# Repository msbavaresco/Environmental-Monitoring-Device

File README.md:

# Environmental Monitoring Device
This project is a device that measures CO2 concentration, temperature and relative humididty using Sensirion's SCD4x sensor and a Raspberry Pi Zero W. The data is then stored internally and, optionally, transmitted via MQTT.

## Hardware Requirements
- Raspberry Pi Zero W
- Sensirion SCD41 or SCD40 sensor

## Wiring
| SCD4x Pin | Raspberry Pi Pin |
|-----------|------------------|
| VCC       | 3.3V             |
| GND       | GND              |
| SDA       | GPIO2 (Pin 3)    |
| SCL       | GPIO3 (Pin 5)    |

## Installation

### 1. Clone the repository

```bash
git clone https://github.com/msbavaresco/Environmental-Monitoring-Device.git
cd Environmental-Monitoring-Device
```

### 2. Install required packages

```bash
sudo apt update
sudo apt install -y \
    build-essential \
    gcc \
    g++ \
    make \
    libpaho-mqttpp3-dev \
    nlohmann-json3-dev
```

### 3. Enable I2C on the Raspberry Pi

Run:

```bash
sudo raspi-config
```

Then go to:

```text
Interface Options -> I2C -> Enable
```

Reboot:

```bash
sudo reboot
```

After reboot, return to the project folder:

```bash
cd Environmental-Monitoring-Device
```

### 4. Create the configuration directory

```bash
sudo mkdir -p /var/lib/ThisDevice
```

### 5. Copy the example configuration file

```bash
sudo cp Source/config/config.example.json /var/lib/ThisDevice/config.json
```

### 6. Edit the configuration file

```bash
sudo nano /var/lib/ThisDevice/config.json
```

Example:

```json
{
  "wifi": {
    "configured": true,
    "ssid": "MyWifi"
  },
  "mqtt": {
    "host": "192.168.1.50",
    "port": 1883,
    "username": "",
    "password": "",
    "base_topic": "env"
  },
  "device": {
    "location": "office"
  }
}
```

### 7. Build the project

```bash
cd Source
make
```

### 8. Run the program

```bash
./bin/project
```

## Notes

- The configuration file must exist at `/var/lib/ThisDevice/config.json`
- I²C must be enabled or the sensor will not work
- Update the MQTT settings and device location before running

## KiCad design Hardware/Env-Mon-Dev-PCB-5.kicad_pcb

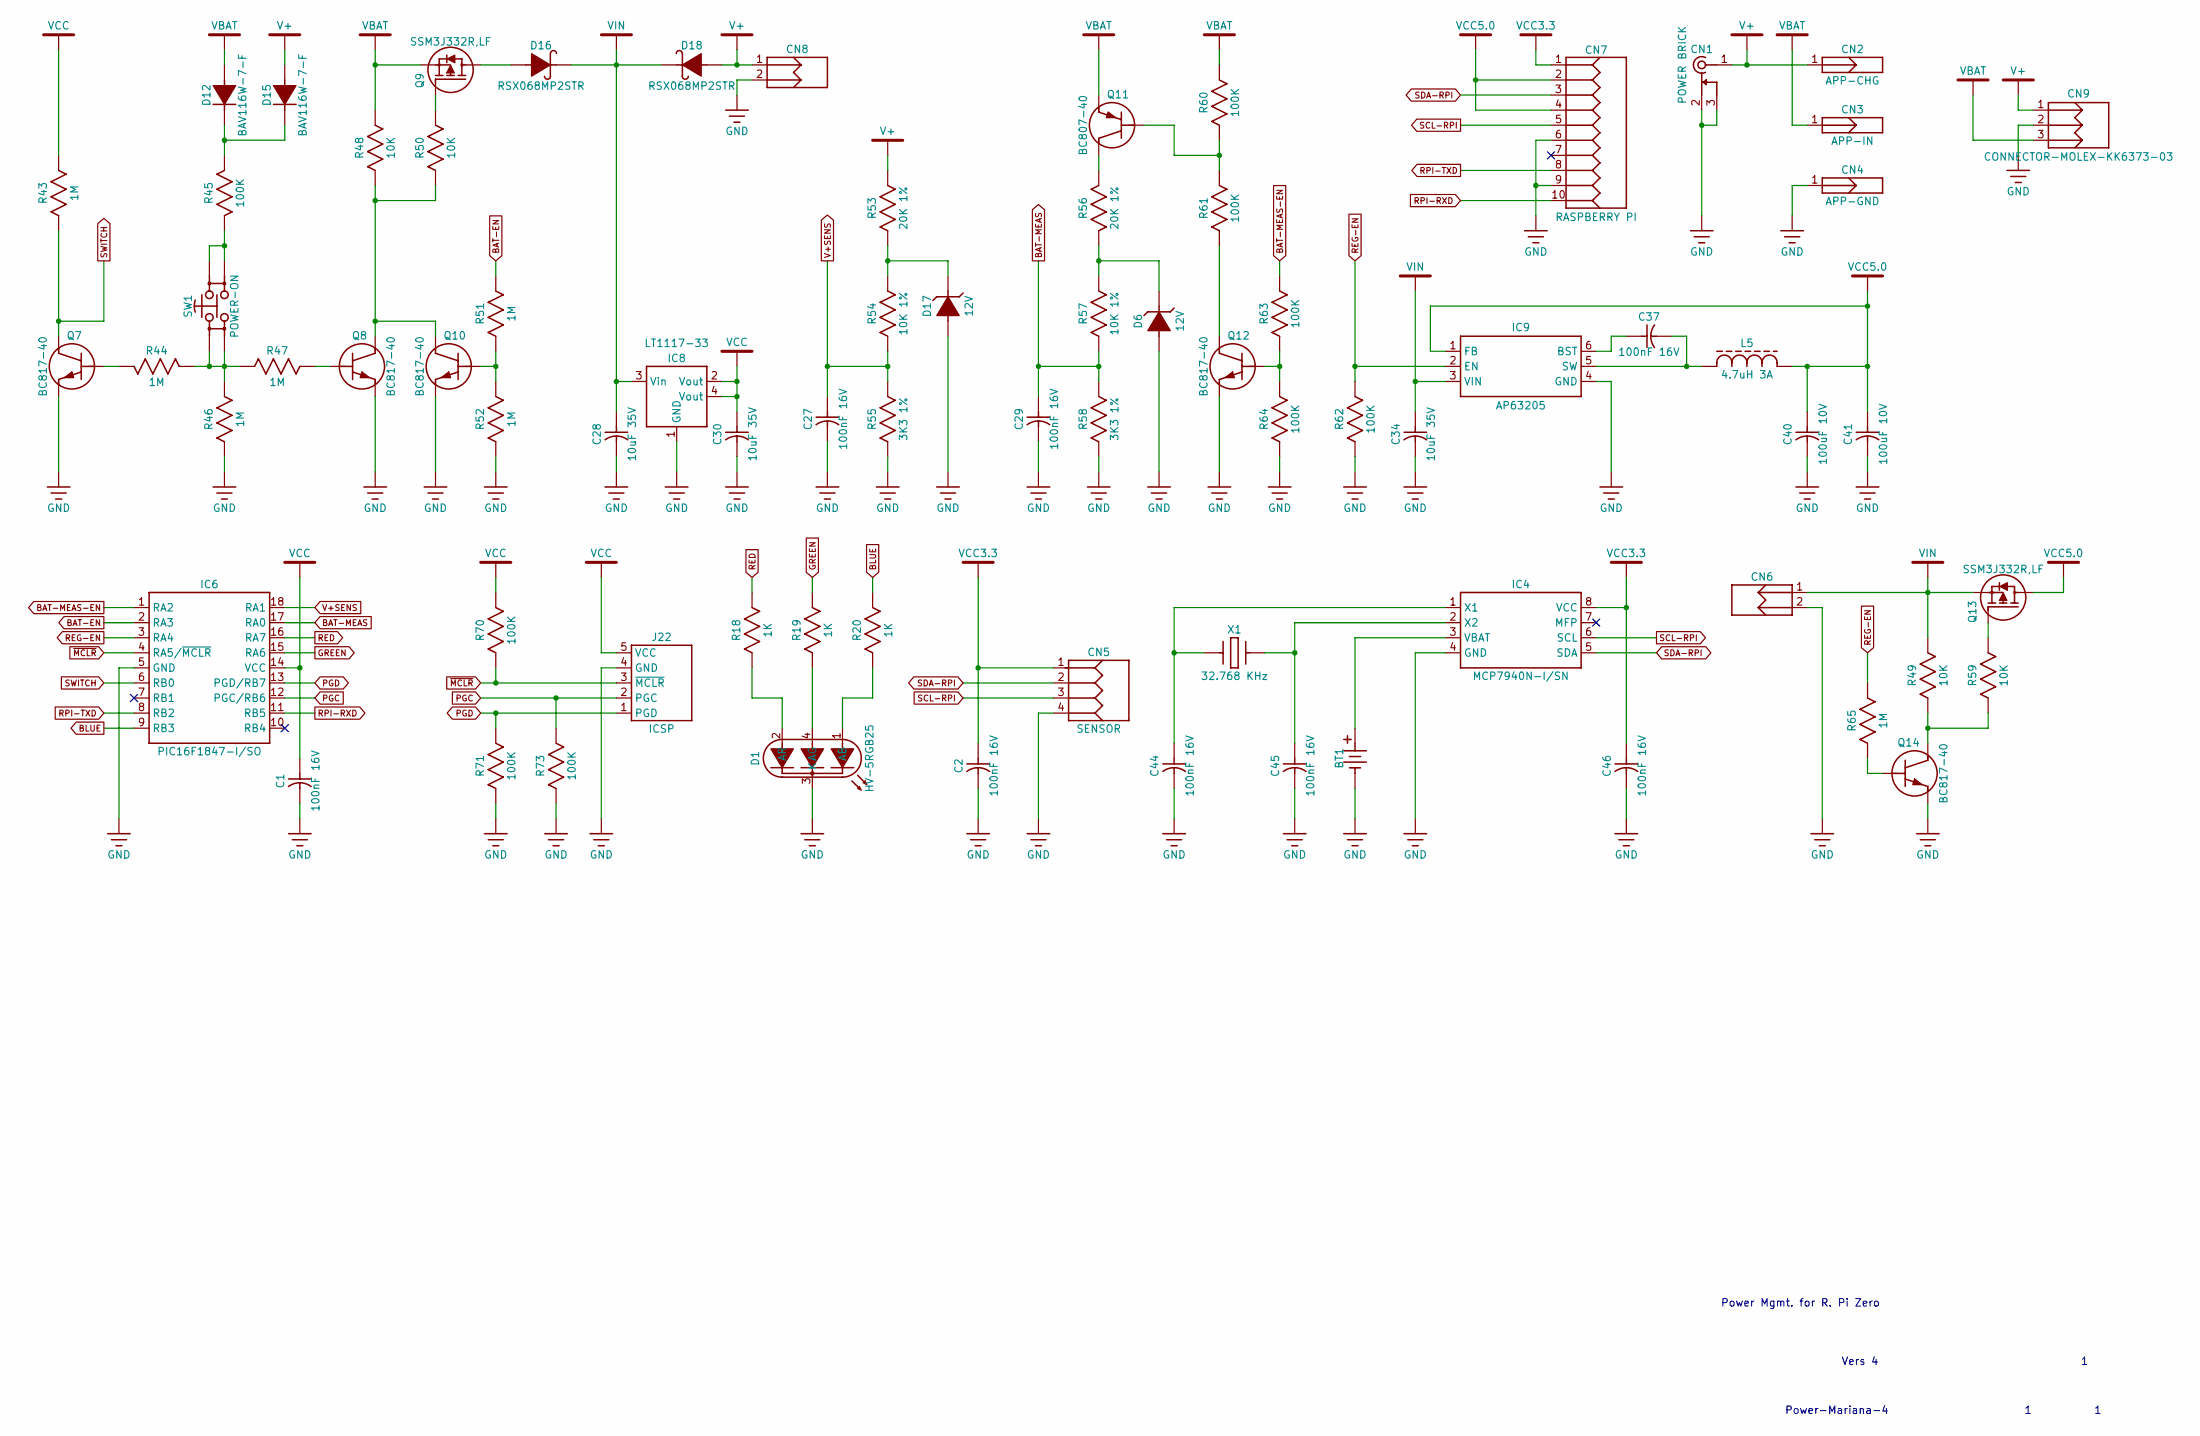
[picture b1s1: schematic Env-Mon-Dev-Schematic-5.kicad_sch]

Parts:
BT1: SOCKET-BATTERY-CR2032
C1, C2, C27, C29, C37, C44, C45, C46: 100nF 16V; CAPACITOR-CC0603R
C28, C30, C34: 10uF 35V; CAPACITOR-CC0805R
C40, C41: 100uF 10V; CAPACITOR-CC1210R
CN1: POWER BRICK; CONNECTOR-JACK-J4-HORIZ
CN2: APP-CHG; CONNECTOR-POGO-01-D3.0H1.0
CN3: APP-IN; CONNECTOR-POGO-01-D3.0H1.0
CN4: APP-GND; CONNECTOR-POGO-01-D3.0H1.0
CN5: SENSOR; CONNECTOR-RECEPTACLE-1X4-P2.54
CN6, CN8: CONNECTOR-MOLEX-KK6373-02
CN7: RASPBERRY PI; CONNECTOR-RECEPTACLE-2X5-P2.54
CN9: CONNECTOR-MOLEX-KK6373-03
D1: HV-5RGB25; LED-RGB-D5.00-P1.588-4P
D6, D17: 12V; SOD-123
D12, D15: BAV116W-7-F; SOD-123
D16, D18: RSX068MP2STR; SOD-123
IC4: MCP7940N-I/SN; SOIC-08-150
IC6: PIC16F1847-I/SO; SOIC-18-300
IC8: LT1117-33; SOT-223
IC9: AP63205; SOT-23-6
J22: ICSP; CONNECTOR-HEADER-1X5-P2.54
L5: 4.7uH 3A; INDUCTOR-FERRITE-NRS6045T
Q7, Q8, Q10, Q12, Q14: BC817-40; SOT-23
Q9, Q13: SSM3J332R,LF; SOT-23
Q11: BC807-40; SOT-23
R18, R19, R20: 1K; RESISTOR-RC0603R
R43, R44, R46, R47, R51, R52, R65: 1M; RESISTOR-RC0603R
R45, R60, R61, R62, R63, R64, R70, R71, R73: 100K; RESISTOR-RC0603R
R48, R49, R50, R59: 10K; RESISTOR-RC0603R
R53, R56: 20K 1%; RESISTOR-RC0805R
R54, R57: 10K 1%; RESISTOR-RC0603R
R55, R58: 3K3 1%; RESISTOR-RC0603R
SW1: POWER-ON; SWITCH-TACTILE-MINI-VERTICAL
X1: 32.768 KHz; CRYSTAL-3.20X1.50-2P

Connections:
BAT-EN: IC6.2 (RA3), R51.2
BAT-MEAS: C29.1, IC6.17 (RA0), R57.1, R58.2
BAT-MEAS-EN: IC6.1 (RA2), R63.2
BLUE: IC6.9 (RB3), R20.2
GND: BT1.2 (-), C1.2, C2.2, C27.2, C28.2, C29.2, C30.2, C34.2, C40.2, C41.2, C44.2, C45.2, C46.2, CN1.2, CN1.3, CN4.1, CN5.4, CN6.2, CN7.6, CN7.9, CN8.2, CN9.2, D1.3 (K), D6.A, D17.A, IC4.4 (GND), IC6.5 (GND), IC8.1 (GND), IC9.4 (GND), J22.4 (GND), Q7.2 (E), Q8.2 (E), Q10.2 (E), Q12.2 (E), Q14.2 (E), R46.1, R52.1, R55.1, R58.1, R62.1, R64.1, R71.1, R73.1
GREEN: IC6.15 (RA6), R19.2
unnamed: BT1.1 (+), IC4.3 (VBAT)
unnamed: D1.1 (AB), R20.1
unnamed: D1.4 (AG), R19.1
unnamed: D1.2 (AR), R18.1
unnamed: D6.K, R56.2, R57.2
unnamed: D12.K, D15.K, R45.1
unnamed: D17.K, R53.1, R54.2
unnamed: C44.1, IC4.1 (X1), X1.1
unnamed: C45.1, IC4.2 (X2), X1.2
unnamed: C37.1, IC9.6 (BST)
unnamed: C37.2, IC9.5 (SW), L5.1
unnamed: Q7.1 (B), R44.2
unnamed: Q8.1 (B), R47.2
unnamed: D16.A, Q9.3 (D)
unnamed: Q9.1 (G), R50.2
unnamed: Q10.1 (B), R51.1, R52.2
unnamed: Q8.3 (C), Q10.3 (C), R48.1, R50.1
unnamed: Q11.1 (B), R60.1, R61.2
unnamed: Q11.3 (C), R56.1
unnamed: Q12.1 (B), R63.1, R64.2
unnamed: Q12.3 (C), R61.1
unnamed: Q13.1 (G), R59.2
unnamed: Q14.1 (B), R65.1
unnamed: Q14.3 (C), R49.1, R59.1
unnamed: R44.1, R46.2, R47.1, SW1.3, SW1.4
unnamed: R45.2, SW1.1, SW1.2
PGC: IC6.12 (PGC/RB6), J22.2 (PGC), R73.2
PGD: IC6.13 (PGD/RB7), J22.1 (PGD), R71.2
RED: IC6.16 (RA7), R18.2
REG-EN: IC6.3 (RA4), IC9.2 (EN), R62.2, R65.2
RPI-RXD: CN7.10, IC6.11 (RB5)
RPI-TXD: CN7.8, IC6.8 (RB2)
SCL-RPI: CN5.3, CN7.5, IC4.6 (SCL)
SDA-RPI: CN5.2, CN7.3, IC4.5 (SDA)
SWITCH: IC6.6 (RB0), Q7.3 (C), R43.1
V+: CN1.1, CN2.1, CN8.1, CN9.1, D15.A, D18.A, R53.2
V+SENS: C27.1, IC6.18 (RA1), R54.1, R55.2
VBAT: CN3.1, CN9.3, D12.A, Q9.2 (S), Q11.2 (E), R48.2, R60.2
VCC: C1.1, C30.1, IC6.14 (VCC), IC8.2 (Vout), IC8.4 (Vout), J22.5 (VCC), R43.2, R70.2
VCC3.3: C2.1, C46.1, CN5.1, CN7.1, IC4.8 (VCC)
VCC5.0: C40.1, C41.1, CN7.2, CN7.4, IC9.1 (FB), L5.2, Q13.3 (D)
VIN: C28.1, C34.1, CN6.1, D16.K, D18.K, IC8.3 (Vin), IC9.3 (VIN), Q13.2 (S), R49.2
~MCLR: IC6.4 (RA5/~MCLR), J22.3 (~MCLR), R70.1

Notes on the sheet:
Power Mgmt. for R. Pi Zero
Vers 4
Power-Mariana-4

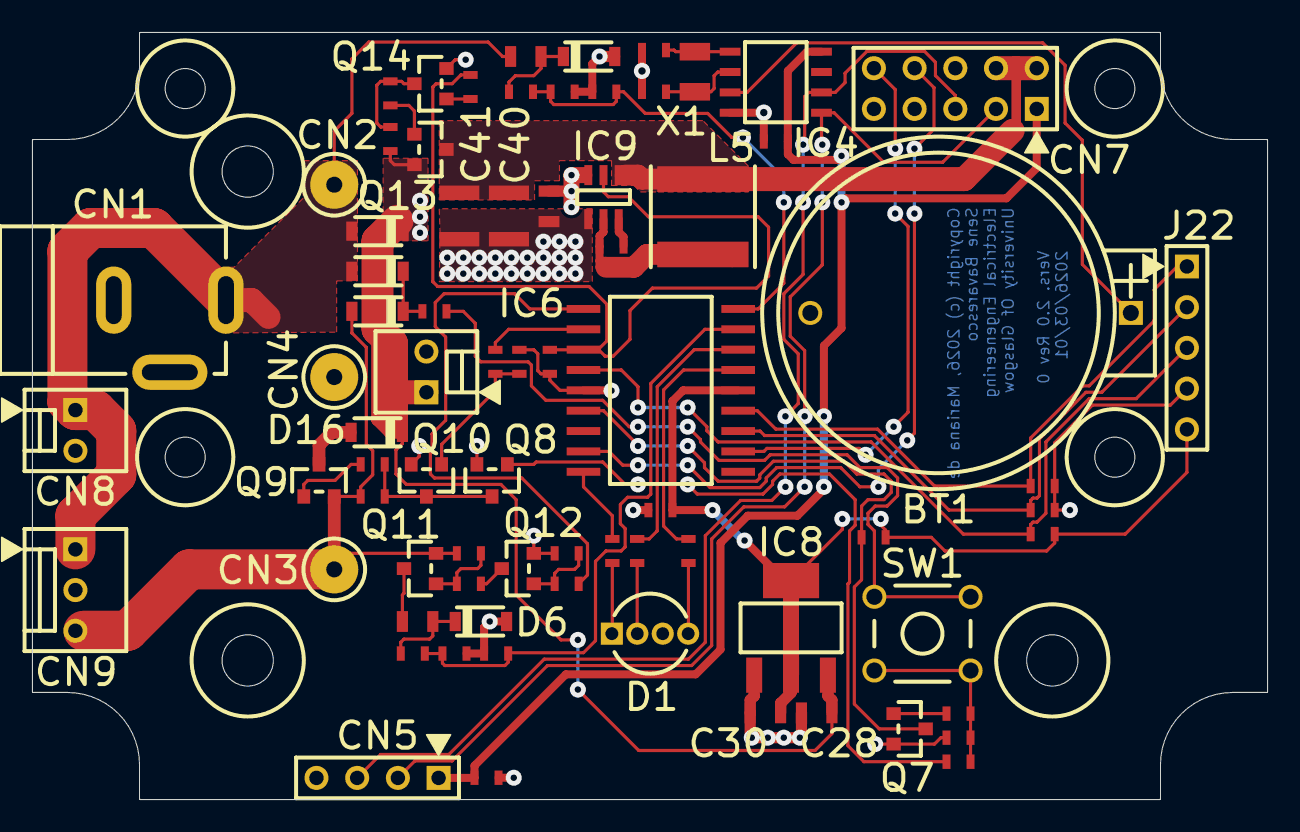
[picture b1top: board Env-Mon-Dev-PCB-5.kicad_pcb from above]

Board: 2 copper layers, 77.1 x 47.9 mm, 75 parts (0 on the bottom side), 49 nets.

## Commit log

2025-11-17 Create LICENSE
2025-11-18 Created routine for reading the sensor.
2025-11-19 Added main.cpp
2025-11-19 Included Sensirion and CppTimer files.
2025-11-20 Replaced the corrupted Sensirion files.
2025-11-20 Changed Makefile.
2025-11-23 Sensor reading working.
2026-03-10 Updated main.cpp
    Currently under testing at the Hunterian Museum.
2026-03-10 Updated Makefile
    Currently under testing at the Hunterian Museum.
2026-03-10 Create Hardware
2026-03-10 Added schematic and PCB
2026-03-17 Added Raspberry Pi power management schematic.
2026-03-17 Refactor: rename SCD4xReading file, convert to C++ struct, add timestamp
2026-03-18 Refactor: create header file for config data, transform JSONReader into a class
2026-03-18 Refactor: transform Save_Data() into a separate class
2026-03-18 Add comments
2026-03-18 New: create DataCleaner class
2026-03-18 Refactor: put MQTT publishing in its own class
2026-03-19 Refactor: Make client an attribute of the class, create client and connect only once
2026-03-19 Refactor: rename variable interval to interval_minutes
2026-03-19 Refactor: update variable name to interval_minutes
2026-03-19 Refactor: add class to handle CppTimer initialization and readings
2026-03-19 Add CppTimer.h
2026-03-19 Refactor: rewrite main using callbacks and signalfd
2026-03-19 Migrate project from Makefile to CMake
2026-03-19 Fix: link Paho MQTT directly in CMake
2026-03-19 Refactor: switch to ordered_json to preserve field order

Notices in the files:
Hardware/Env-Mon-Dev-PCB-5.kicad_pcb:
Copyright (c) 2026, Mariana de
